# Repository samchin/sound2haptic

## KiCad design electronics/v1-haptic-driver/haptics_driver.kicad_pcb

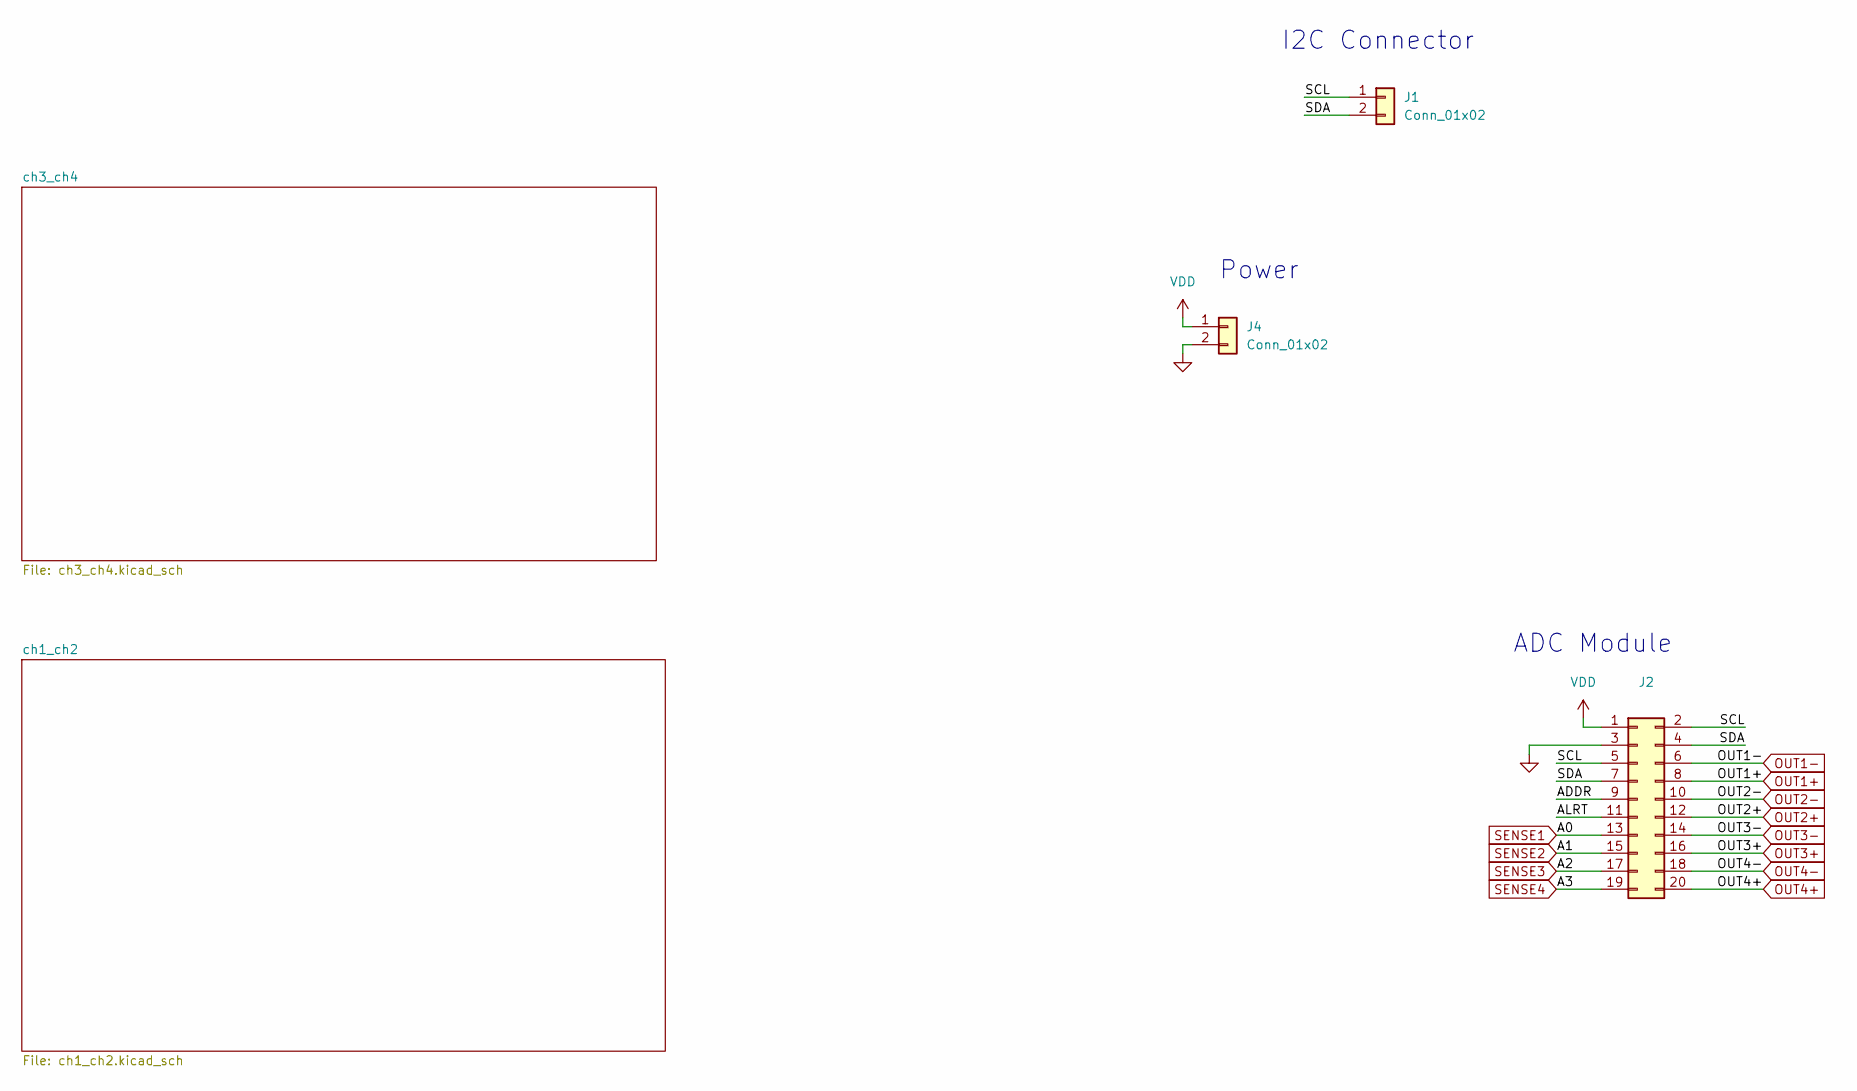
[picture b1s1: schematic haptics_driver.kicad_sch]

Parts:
J1, J4: Conn_01x02; PinHeader_1x02_P2.54mm_Vertical
J2: Conn_02x10_Odd_Even; PinHeader_2x10_P2.54mm_Vertical_SMD

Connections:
/ADDR: J2.9
/ALRT: J2.11
/SCL: J1.1, J2.2, J2.5
/SDA: J1.2, J2.4, J2.7
GND: J2.3, J4.2; also elsewhere on the board
OUT1+: J2.8; also elsewhere on the board
OUT1-: J2.6; also elsewhere on the board
OUT2+: J2.12; also elsewhere on the board
OUT2-: J2.10; also elsewhere on the board
OUT3+: J2.16; also elsewhere on the board
OUT3-: J2.14; also elsewhere on the board
OUT4+: J2.20; also elsewhere on the board
OUT4-: J2.18; also elsewhere on the board
SENSE1: J2.13; also elsewhere on the board
SENSE2: J2.15; also elsewhere on the board
SENSE3: J2.17; also elsewhere on the board
SENSE4: J2.19; also elsewhere on the board
VDD: J2.1, J4.1; also elsewhere on the board

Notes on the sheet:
ADC Module
Power
I2C Connector

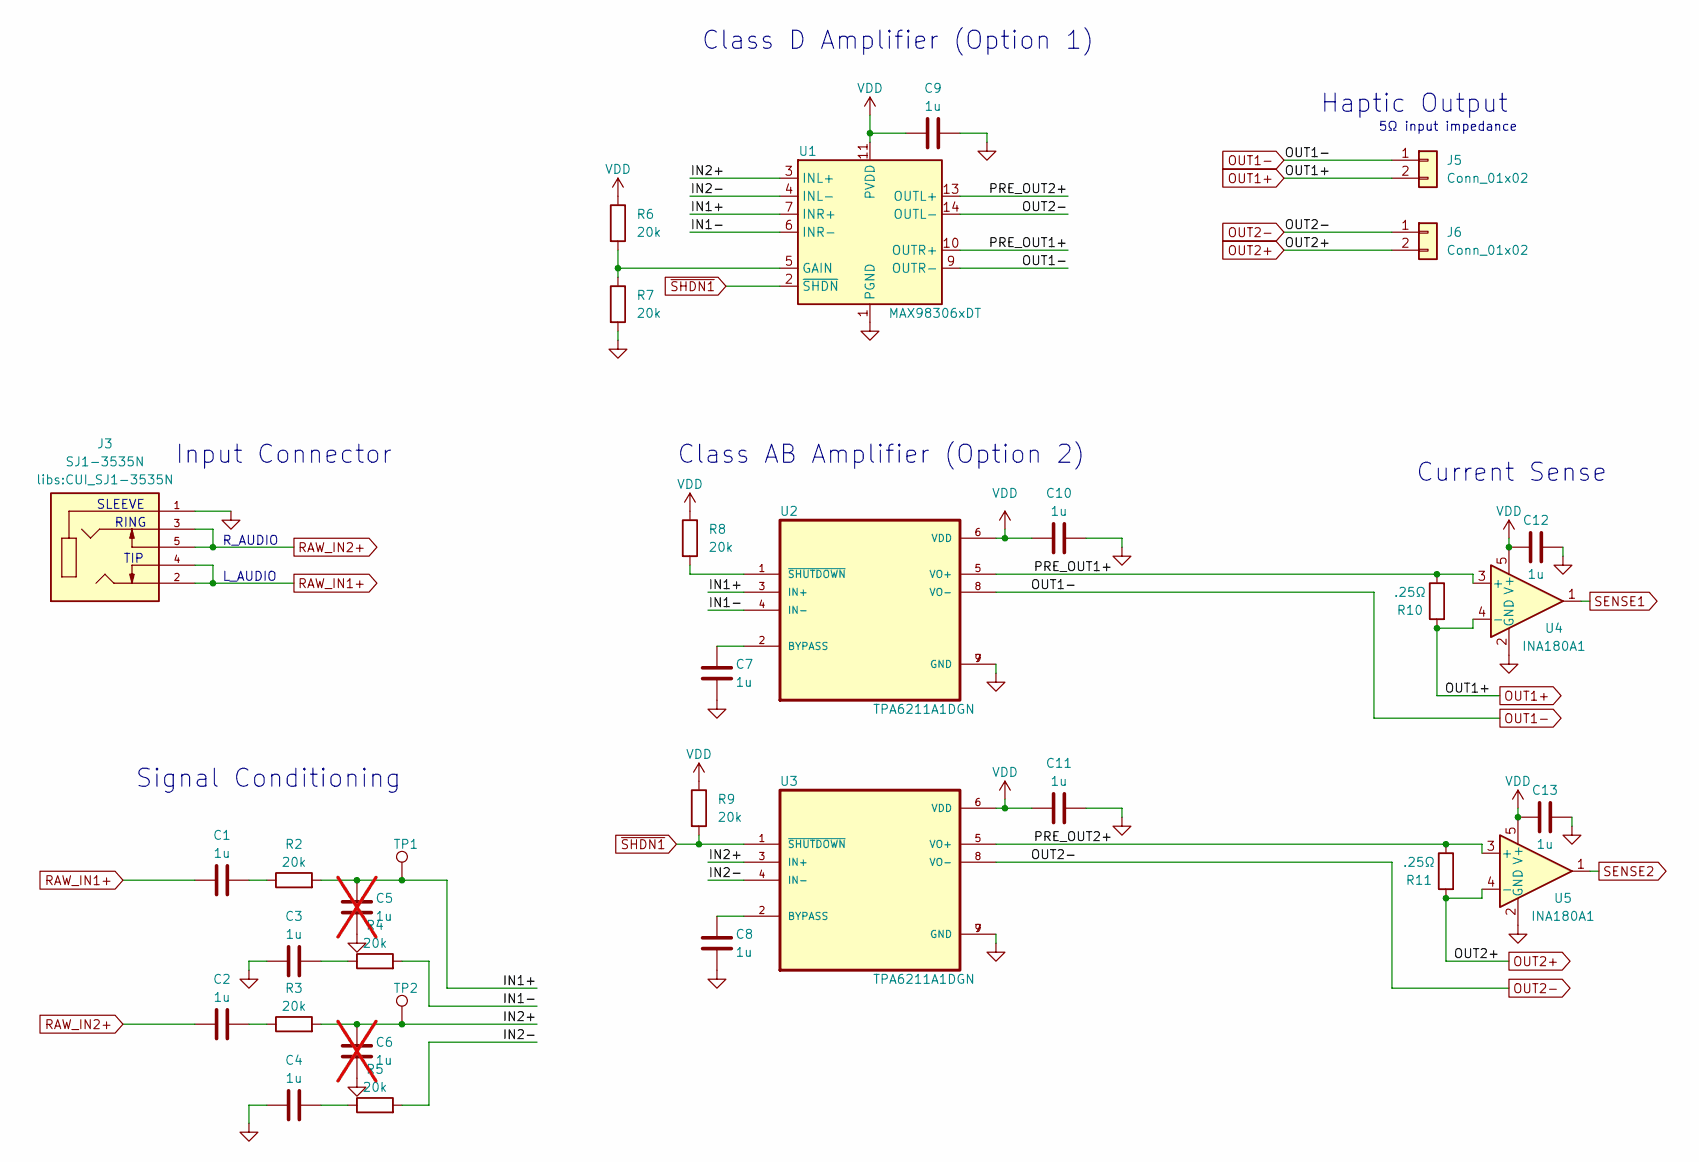
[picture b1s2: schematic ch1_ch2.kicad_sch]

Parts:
C1, C2, C3, C4, C7, C8, C9, C10, C11, C12, C13: 1u; C_0603_1608Metric
C5, C6: 1u; C_0603_1608Metric; not fitted
J3: SJ1-3535N; CUI_SJ1-3535N; PARTREV 1.03
J5, J6: Conn_01x02; PinHeader_1x02_P2.54mm_Vertical
R2, R3, R4, R5, R6, R7, R8, R9: 20k; R_0603_1608Metric
R10, R11: .25Ω; R_0805_2012Metric
TP1, TP2: TestPoint; TestPoint_THTPad_2.0x2.0mm_Drill1.0mm
U1: MAX98306xDT; TDFN-14-1EP_3x3mm_P0.4mm_EP1.78x2.35mm
U2, U3: TPA6211A1DGN; SOP65P490X110-9N
U4, U5: INA180A1; SOT-23-5

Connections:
/ch1_ch2/IN1+: C5.1, R2.2, TP1.1, U1.7 (INR+), U2.3 (IN+)
/ch1_ch2/IN1-: R4.2, U1.6 (INR-), U2.4 (IN-)
/ch1_ch2/IN2+: C6.1, R3.2, TP2.1, U1.3 (INL+), U3.3 (IN+)
/ch1_ch2/IN2-: R5.2, U1.4 (INL-), U3.4 (IN-)
/ch1_ch2/PRE_OUT1+: R10.1, U1.10 (OUTR+), U2.5 (VO+), U4.3 (+)
/ch1_ch2/PRE_OUT2+: R11.1, U1.13 (OUTL+), U3.5 (VO+), U5.3 (+)
GND: C3.1, C4.1, C5.2, C6.2, C7.2, C8.2, C9.2, C10.2, C11.2, C12.2, C13.2, J3.1, R7.2, U1.1 (PGND), U1.8 (PGND), U1.15 (PGND), U2.7 (GND), U2.9 (GND), U3.7 (GND), U3.9 (GND), U4.2 (GND), U5.2 (GND); also elsewhere on the board
unnamed: C1.2, R2.1
unnamed: C2.2, R3.1
unnamed: C3.2, R4.1
unnamed: C4.2, R5.1
unnamed: R6.2, R7.1, U1.5 (GAIN)
unnamed: C7.1, U2.2 (BYPASS)
unnamed: R8.2, U2.1 (~SHUTDOWN)
unnamed: C8.1, U3.2 (BYPASS)
OUT1+: J5.2, R10.2, U4.4 (-); also elsewhere on the board
OUT1-: J5.1, U1.9 (OUTR-), U2.8 (VO-); also elsewhere on the board
OUT2+: J6.2, R11.2, U5.4 (-); also elsewhere on the board
OUT2-: J6.1, U1.14 (OUTL-), U3.8 (VO-); also elsewhere on the board
RAW_IN1+: C1.1, J3.2, J3.4
RAW_IN2+: C2.1, J3.3, J3.5
SENSE1: U4.1; also elsewhere on the board
SENSE2: U5.1; also elsewhere on the board
VDD: C9.1, C10.1, C11.1, C12.1, C13.1, R6.1, R8.1, R9.1, U1.11 (PVDD), U1.12 (PVDD), U2.6 (VDD), U3.6 (VDD), U4.5 (V+), U5.5 (V+); also elsewhere on the board
~SHDN1: R9.2, U1.2 (~SHDN), U3.1 (~SHUTDOWN)

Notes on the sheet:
Signal Conditioning
RING
5Ω input impedance
Input Connector
TIP
Current Sense
Class AB Amplifier (Option 2)
SLEEVE
R_AUDIO
Haptic Output
Class D Amplifier (Option 1)
L_AUDIO

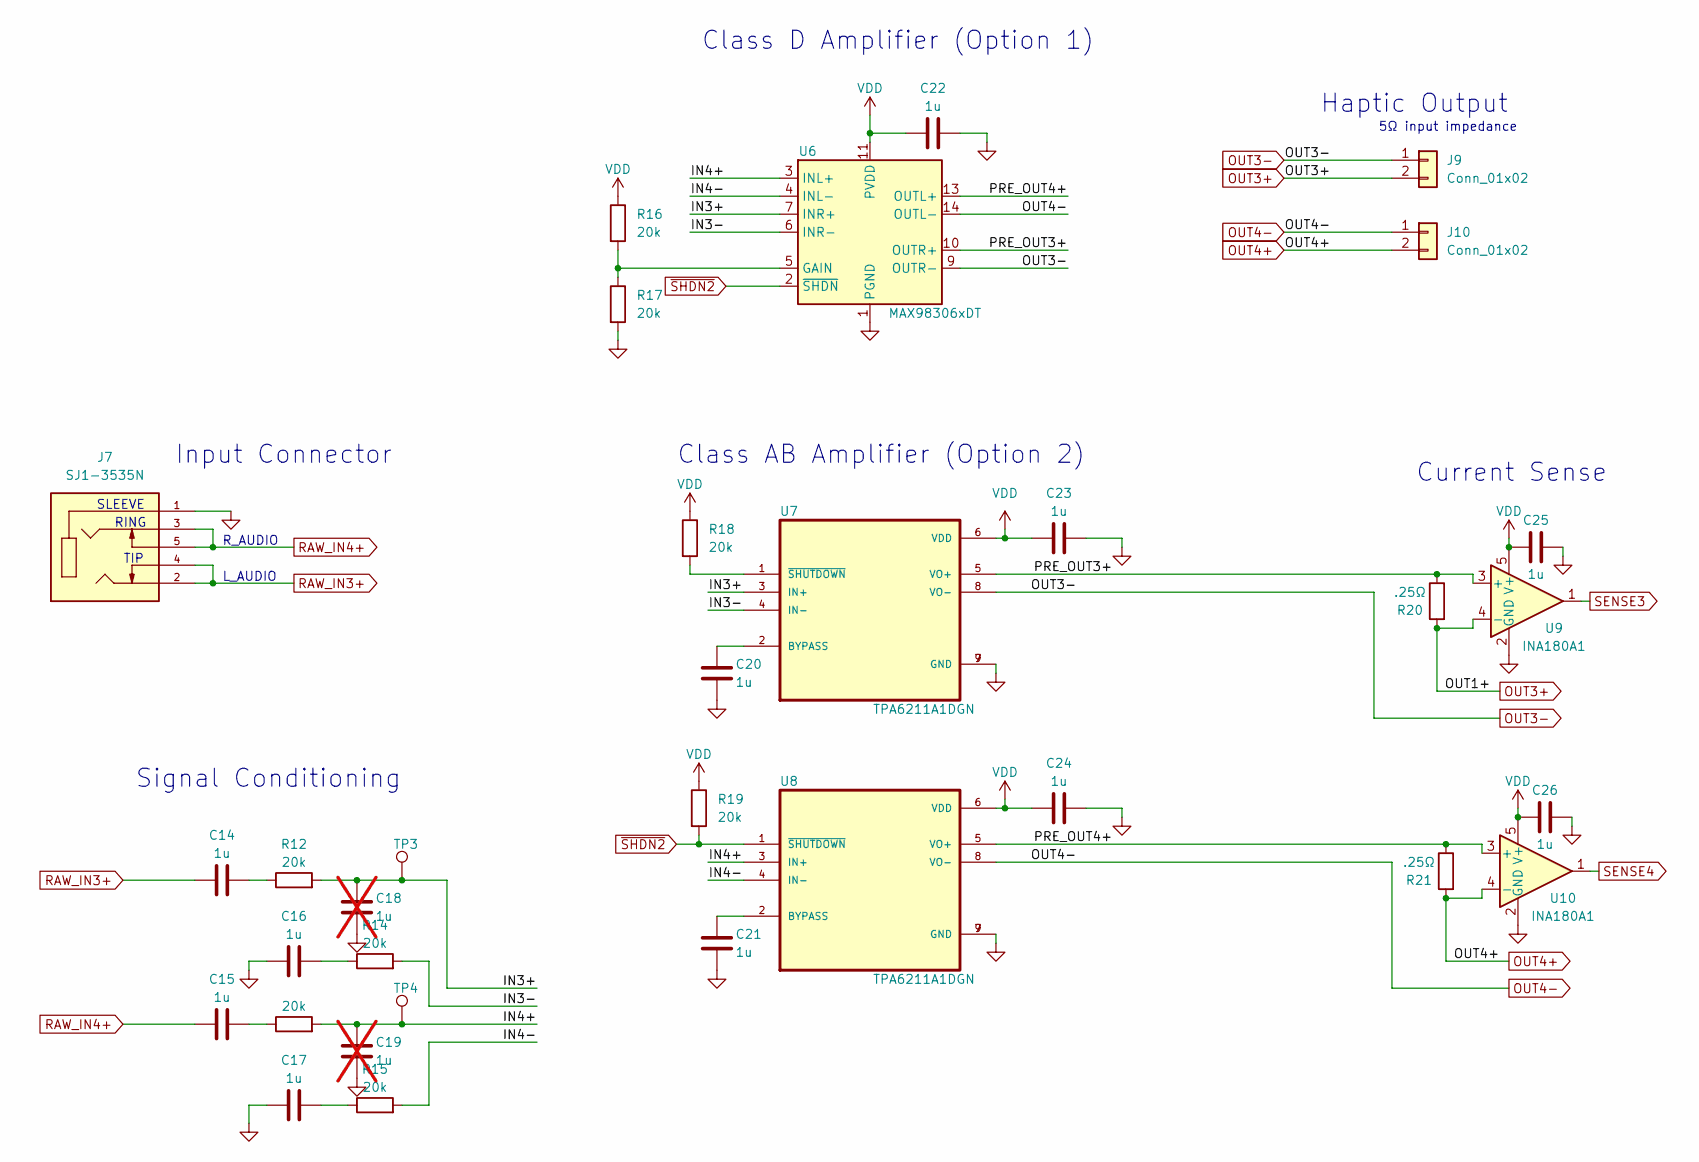
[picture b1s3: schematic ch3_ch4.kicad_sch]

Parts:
C14, C15, C16, C17, C20, C21, C22, C23, C24, C25, C26: 1u; C_0603_1608Metric
C18, C19: 1u; C_0603_1608Metric; not fitted
J7: SJ1-3535N; CUI_SJ1-3535N; PARTREV 1.03
J9, J10: Conn_01x02; PinHeader_1x02_P2.54mm_Vertical
R12, R13, R14, R15, R16, R17, R18, R19: 20k; R_0603_1608Metric
R20, R21: .25Ω; R_0805_2012Metric
TP3, TP4: TestPoint; TestPoint_THTPad_2.0x2.0mm_Drill1.0mm
U6: MAX98306xDT; TDFN-14-1EP_3x3mm_P0.4mm_EP1.78x2.35mm
U7, U8: TPA6211A1DGN; SOP65P490X110-9N
U9, U10: INA180A1; SOT-23-5

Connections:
/ch3_ch4/IN3+: C18.1, R12.2, TP3.1, U6.7 (INR+), U7.3 (IN+)
/ch3_ch4/IN3-: R14.2, U6.6 (INR-), U7.4 (IN-)
/ch3_ch4/IN4+: C19.1, R13.2, TP4.1, U6.3 (INL+), U8.3 (IN+)
/ch3_ch4/IN4-: R15.2, U6.4 (INL-), U8.4 (IN-)
/ch3_ch4/PRE_OUT3+: R20.1, U6.10 (OUTR+), U7.5 (VO+), U9.3 (+)
/ch3_ch4/PRE_OUT4+: R21.1, U6.13 (OUTL+), U8.5 (VO+), U10.3 (+)
GND: C16.1, C17.1, C18.2, C19.2, C20.2, C21.2, C22.2, C23.2, C24.2, C25.2, C26.2, J7.1, R17.2, U6.1 (PGND), U6.8 (PGND), U6.15 (PGND), U7.7 (GND), U7.9 (GND), U8.7 (GND), U8.9 (GND), U9.2 (GND), U10.2 (GND); also elsewhere on the board
unnamed: C14.2, R12.1
unnamed: C15.2, R13.1
unnamed: C16.2, R14.1
unnamed: C17.2, R15.1
unnamed: R16.2, R17.1, U6.5 (GAIN)
unnamed: C20.1, U7.2 (BYPASS)
unnamed: R18.2, U7.1 (~SHUTDOWN)
unnamed: C21.1, U8.2 (BYPASS)
OUT3+: J9.2, R20.2, U9.4 (-); also elsewhere on the board
OUT3-: J9.1, U6.9 (OUTR-), U7.8 (VO-); also elsewhere on the board
OUT4+: J10.2, R21.2, U10.4 (-); also elsewhere on the board
OUT4-: J10.1, U6.14 (OUTL-), U8.8 (VO-); also elsewhere on the board
RAW_IN3+: C14.1, J7.2, J7.4
RAW_IN4+: C15.1, J7.3, J7.5
SENSE3: U9.1; also elsewhere on the board
SENSE4: U10.1; also elsewhere on the board
VDD: C22.1, C23.1, C24.1, C25.1, C26.1, R16.1, R18.1, R19.1, U6.11 (PVDD), U6.12 (PVDD), U7.6 (VDD), U8.6 (VDD), U9.5 (V+), U10.5 (V+); also elsewhere on the board
~SHDN2: R19.2, U6.2 (~SHDN), U8.1 (~SHUTDOWN)

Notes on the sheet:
Signal Conditioning
RING
5Ω input impedance
Input Connector
TIP
Current Sense
Class AB Amplifier (Option 2)
SLEEVE
R_AUDIO
Haptic Output
Class D Amplifier (Option 1)
L_AUDIO

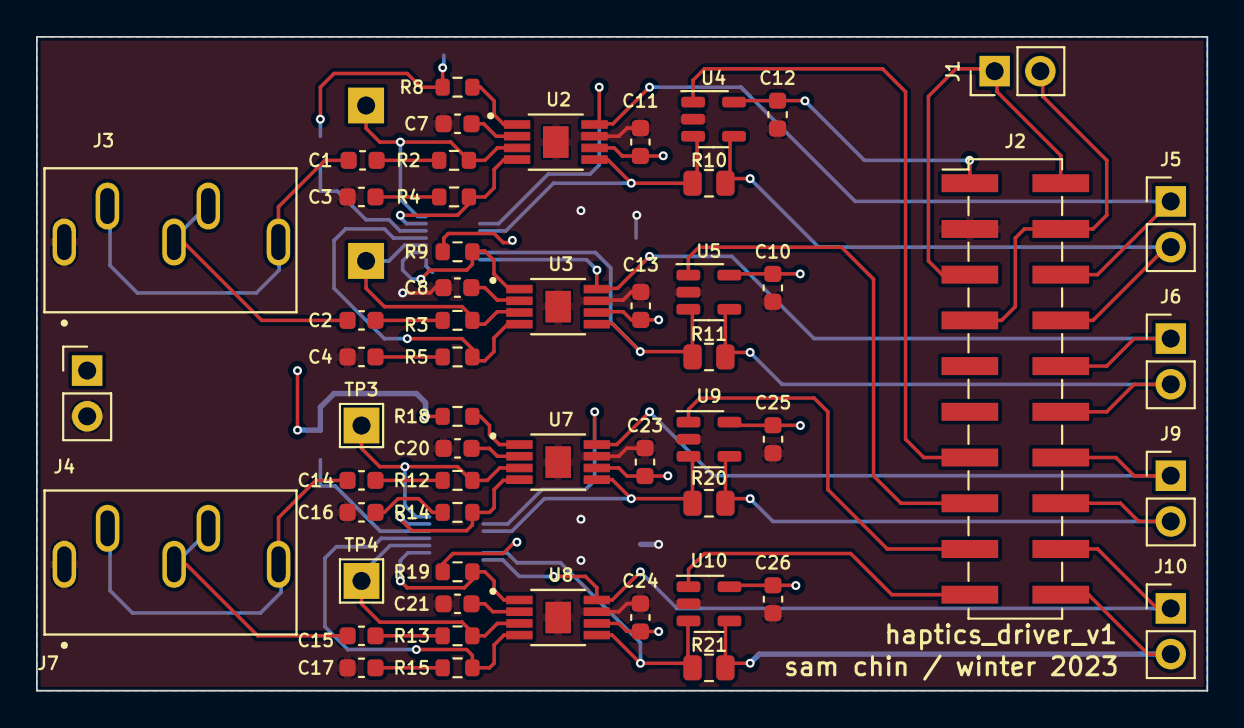
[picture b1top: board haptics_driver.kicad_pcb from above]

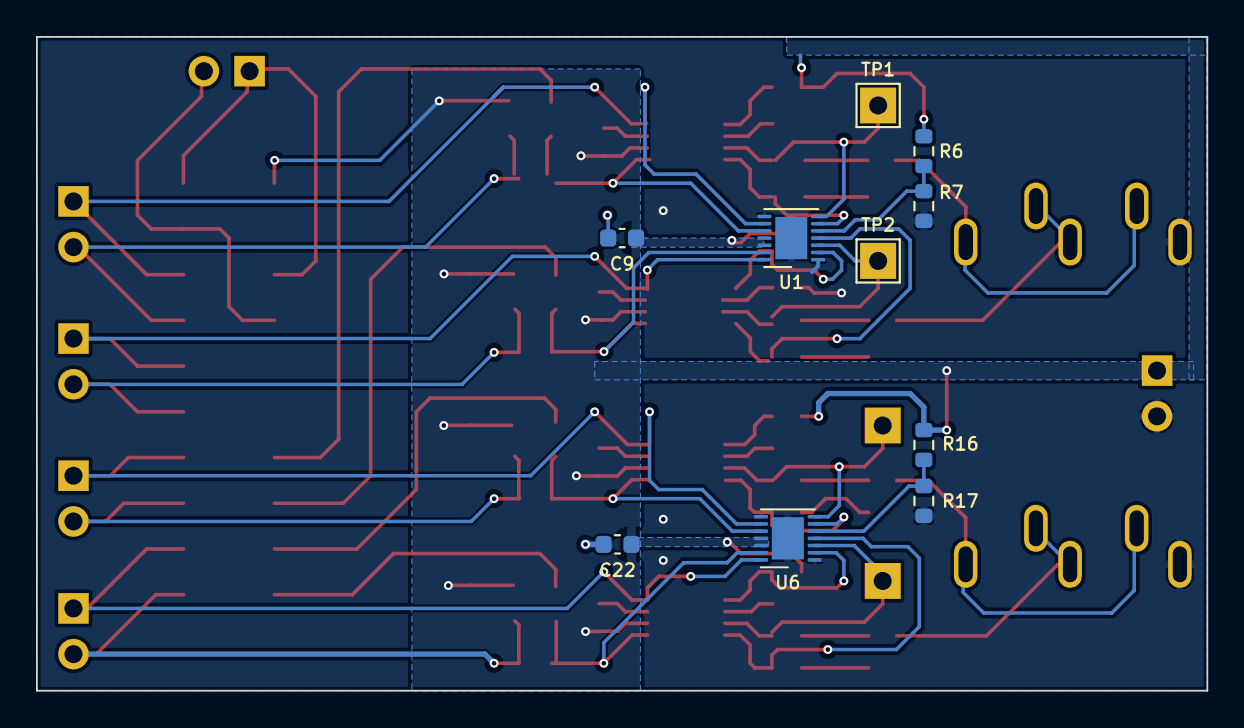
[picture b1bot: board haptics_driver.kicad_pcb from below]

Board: 2 copper layers, 65.0 x 36.3 mm, 65 parts (10 on the bottom side), 50 nets.

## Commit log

2025-09-18 Add AudioBoard and sound2hap as submodules
2025-09-18 initial structure
